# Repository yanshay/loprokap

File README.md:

# LoProKap

A wireless split keyboard with keys layout somewhat compatible with Kinesis Advantage Pro 360<sup>TM</sup>.
Designed using [Ergogen](https://ergogen.xyz/) and my [Ergogen Routing System](https://github.com/yanshay/ergogen-stuff)

> **Warning**
>
> This keyboard is still under development and not ready for manufacturing.

## Background

I own a [Kinesis Advantage Pro 360 keyboard](https://kinesis-ergo.com/shop/adv360pro/). 

With its concave structure, ergonomically it's a **great** keyboard but that costs in it not being very mobile.

Since I started using it I find it uncomfortable/confusing to use a standard keyboard when the Kinesis is not with me, so wanted to build a more mobile low profile keyboard that shares the same zmk configuration, and for that needed a compatible key layout. I also wanted keys to be layed out in a way that works on a non concave keyboard. This keyboard is the result.

The keyboard is developed using Ergogen and KiCad.

Ergogen is geat for layout of keys and other components however lacks any support for routing the PCB. With basic Ergogen usage every change in Ergogen cofig requires routing the keyboard from scratch.

Faced with that challenge, I developed a system for easy routing that complements Ergogen, where the routes are 'recorded' in Kicad as Ergogen footprint config using a KiCad plugin + routes are generated by Ergogen using the router footprint.

Both the KiCad Plugin and the Ergogen Footprint are available at https://github.com/yanshay/ergogen-stuff .

## Building the keyboard

1. Clone this repo
2. Change into the ergogen_src/footprints and execute the download_fps.sh to fetch the footprints from the relevant repositories
3. From the root folder run Build.sh
4. Output pcbs will be in pcbs folder (the repository already includes a version of the built pcb)

There are several scripts at the repo root that are specific to my systm folder structure that include some helpful functionality for easier workflow with Ergogen.

## Credits and Acknowledgements
- [Ergogen](https://ergogen.xyz/)

- [@infused-kim](https://github.com/infused-kim)
  - https://github.com/infused-kim/kb_ergogen_fp - basis for the footprints used, some of them were improved for this keyboard and therefore are in this repo
  - https://github.com/infused-kim/kb_think_corney - referenced used for learning
  - Thanks for the assistance over Ergogen Discord

- Everyone else who contributed to @infused-kim work and are mentioned in his repos, so indirectly contributed to this as well.

## License

**TLDR:**

- Personal use with attribution
- Commercial use not allowed
- Distribution under same license as the original

This work is licensed under a
[Creative Commons Attribution-ShareAlike 4.0 International License][cc-by-sa].

[![CC BY-SA 4.0][cc-by-sa-image]][cc-by-sa]

[cc-by-sa]: http://creativecommons.org/licenses/by-sa/4.0/
[cc-by-sa-image]: https://licensebuttons.net/l/by-sa/4.0/88x31.png
[cc-by-sa-shield]: https://img.shields.io/badge/License-CC%20BY--SA%204.0-lightgrey.svg

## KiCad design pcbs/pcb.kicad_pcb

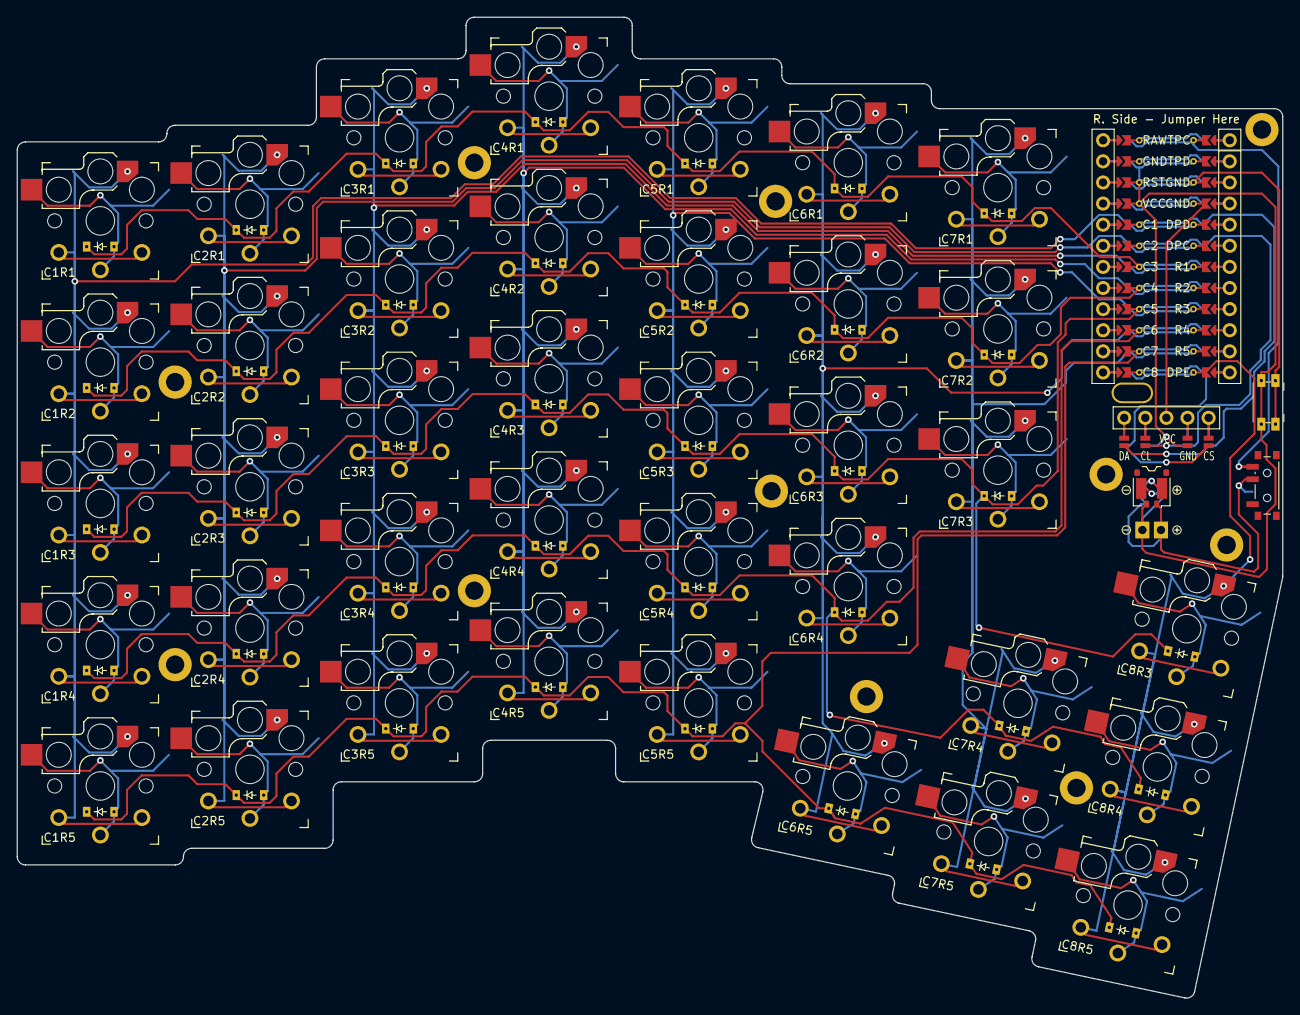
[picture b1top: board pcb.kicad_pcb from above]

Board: 2 copper layers, 152.3 x 118.0 mm, 97 parts (0 on the bottom side), 63 nets.

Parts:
CONN1: conn_molex_pico_ezmate_1x02
D1, D2, D3, D4, D5, D6, D7, D8, D9, D10, D11, D12, D13, D14, D15, D16, D17, D18, D19, D20, D21, D22, D23, D24, D25, D26, D27, D28, D29, D30, D31, D32, D33, D34, D35, D36, D37, D38: ComboDiode
DISP1: nice!view
H1, H2, H3, H4, H5, H6, H7, H8, H9, H10, H11, H12: mounting_hole
ICON1, ICON2: icon_bat
MCU1: nice_nano
PAD1, PAD2: pads
S1, S2, S3, S4, S5, S6, S7, S8, S9, S10, S11, S12, S13, S14, S15, S16, S17, S18, S19, S20, S21, S22, S23, S24, S25, S26, S27, S28, S29, S30, S31, S32, S33, S34, S35, S36, S37, S38: PG1350
SW1: Panasonic_EVQPUJ_EVQPUA
SW2: power_switch

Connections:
BAT_P: CONN1.1, PAD1.1, PAD1.2, PAD2.1, SW2.2, SW2.5
C1: MCU1.5, S1.1, S2.1, S3.1, S4.1, S5.1
C2: MCU1.6, S6.1, S7.1, S8.1, S9.1, S10.1
C3: MCU1.7, S11.1, S12.1, S13.1, S14.1, S15.1
C4: MCU1.8, S16.1, S17.1, S18.1, S19.1, S20.1
C5: MCU1.9, S21.1, S22.1, S23.1, S24.1, S25.1
C6: MCU1.10, S26.1, S27.1, S28.1, S29.1, S33.1
C7: MCU1.11, S30.1, S31.1, S32.1, S34.1, S35.1
C8: MCU1.12, S36.1, S37.1, S38.1
DISP1_1: DISP1.1, DISP1.14, DISP1.27
DISP1_2: DISP1.2, DISP1.15, DISP1.26
DISP1_4: DISP1.4, DISP1.16, DISP1.25
DISP1_5: DISP1.5, DISP1.17, DISP1.24
DPC: DISP1.11, DISP1.21, MCU1.119
DPD: DISP1.10, DISP1.20, MCU1.120
DPE: DISP1.13, DISP1.23, MCU1.113
GND: CONN1.2, DISP1.12, DISP1.22, MCU1.2, MCU1.121, MCU1.122, PAD1.1, PAD1.2, PAD2.2, SW1.1
R1: D5.1, D10.1, D15.1, D20.1, D25.1, D29.1, D32.1, MCU1.118
R2: D4.1, D9.1, D14.1, D19.1, D24.1, D28.1, D31.1, MCU1.117
R3: D3.1, D8.1, D13.1, D18.1, D23.1, D27.1, D30.1, D38.1, MCU1.116
R4: D2.1, D7.1, D12.1, D17.1, D22.1, D26.1, D35.1, D37.1, MCU1.115
R5: D1.1, D6.1, D11.1, D16.1, D21.1, D33.1, D34.1, D36.1, MCU1.114
RAW: MCU1.1, SW2.3, SW2.6
RST: MCU1.3, SW1.2
VCC: DISP1.3, MCU1.4
far_bottom: D36.1, S36.2
far_over: D38.1, S38.2
far_top: D37.1, S37.2
index_bottom: D21.1, S21.2
index_home: D23.1, S23.2
index_low: D22.1, S22.2
index_num: D25.1, S25.2
index_top: D24.1, S24.2
inner_home: D27.1, S27.2
inner_low: D26.1, S26.2
inner_num: D29.1, S29.2
inner_top: D28.1, S28.2
mid_bottom: D34.1, S34.2
mid_top: D35.1, S35.2
middle_bottom: D16.1, S16.2
middle_home: D18.1, S18.2
middle_low: D17.1, S17.2
middle_num: D20.1, S20.2
middle_top: D19.1, S19.2
near_bottom: D33.1, S33.2
outer_bottom: D1.1, S1.2
outer_home: D3.1, S3.2
outer_low: D2.1, S2.2
outer_num: D5.1, S5.2
outer_top: D4.1, S4.2
pinky_bottom: D6.1, S6.2
pinky_home: D8.1, S8.2
pinky_low: D7.1, S7.2
pinky_num: D10.1, S10.2
pinky_top: D9.1, S9.2
ring_bottom: D11.1, S11.2
ring_home: D13.1, S13.2
ring_low: D12.1, S12.2
ring_num: D15.1, S15.2
ring_top: D14.1, S14.2
superinner_home: D30.1, S30.2
superinner_num: D32.1, S32.2
superinner_top: D31.1, S31.2

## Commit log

2023-10-05 Initial commit - first working version
2023-10-05 added kicak_pro file
2023-10-05 switched to download footprints from my fork of infused-kim footprints
2023-10-05 Added readme
2023-10-05 a few updates to readme
2023-10-05 added image of pcb to readme
2023-10-05 updated image
2023-10-05 improved thumb C6R5 route to matrix
2023-10-05 update pcb and image
2023-10-05 added warning to readme
2023-10-05 fixed one router footprint that wasn't locked
2023-10-05 minor update to readme
2023-10-05 updated kicad_pro with jclpcb capabilities
2023-10-05 remove gerber from git
2023-10-05 added display cover mount holes and reorganized around to fit
2023-10-06 some routing improvements and mounting holes adjustments
